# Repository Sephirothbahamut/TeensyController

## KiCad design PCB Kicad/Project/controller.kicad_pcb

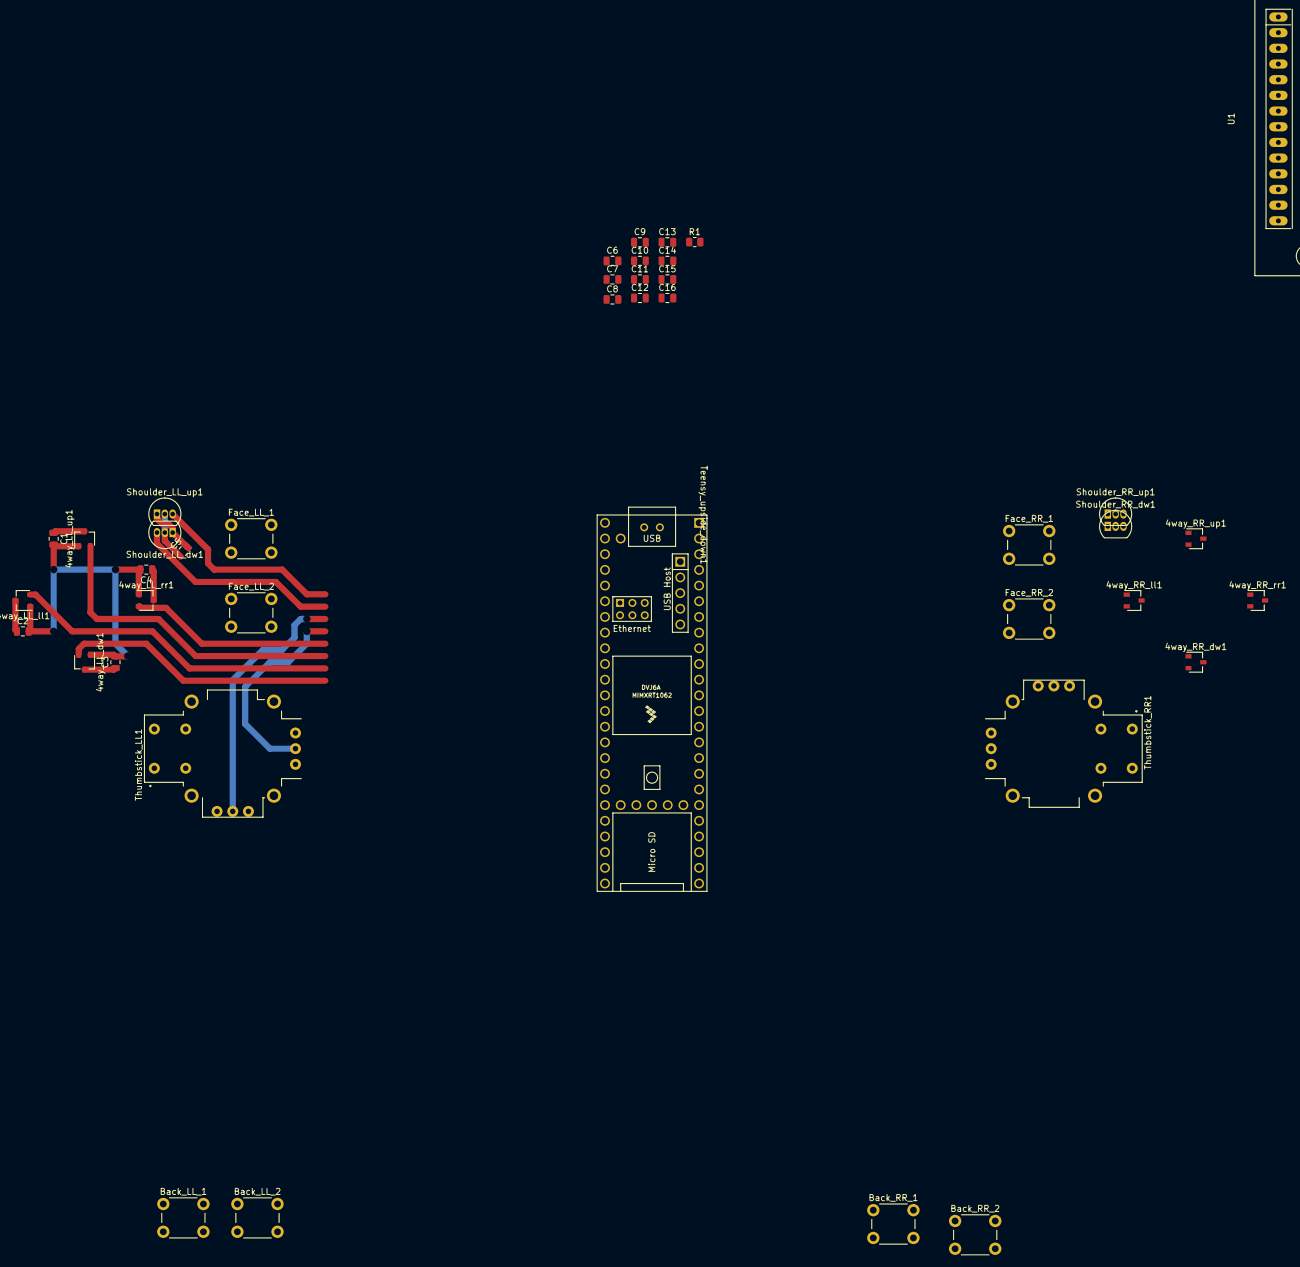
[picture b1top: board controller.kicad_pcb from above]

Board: 2 copper layers, 41 parts (0 on the bottom side), 32 nets.

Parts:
4way_LL_dw1, 4way_LL_ll1, 4way_LL_rr1, 4way_LL_up1, 4way_RR_dw1, 4way_RR_ll1, 4way_RR_rr1, 4way_RR_up1: A3214ELHLT-T; SOT-23W
Back_LL_1, Back_LL_2: SW_MEC_5E; SW_PUSH_6mm
Back_RR_1, Back_RR_2: SW_MEC_5E; SW_PUSH_6mm
C1, C2, C3, C4, C5, C6, C7, C8, C9, C10, C11, C12, C13, C14, C15, C16: Capacitor_SMD; C_0805_2012Metric
Face_LL_1, Face_LL_2: SW_MEC_5E; SW_PUSH_6mm
Face_RR_1, Face_RR_2: SW_MEC_5E; SW_PUSH_6mm
R1: Resistor 100ohm; R_0805_2012Metric
Shoulder_LL_dw1: DRV5055A3xLPGxQ1; TO-92_Inline
Shoulder_LL_up1: DRV5055A3xLPGxQ1; TO-92_Inline
Shoulder_RR_dw1: DRV5055A3xLPGxQ1; TO-92_Inline
Shoulder_RR_up1: DRV5055A3xLPGxQ1; TO-92_Inline
Teensy_upside_down1: Teensy4.1; Teensy41_upside_down
Thumbstick_LL1: Thumbstick; XDCR_COM-09032
Thumbstick_RR1: Thumbstick; XDCR_COM-09032
U1: TFT_320x240; TFT-320x240

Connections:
unnamed: 4way_LL_dw1.3 (GND), 4way_LL_ll1.3 (GND), 4way_LL_rr1.3 (GND), 4way_LL_up1.3 (GND), Back_LL_1.1, Back_LL_1.2, Back_LL_2.1, Back_LL_2.2, C1.1, C2.1, C3.1, C4.1, C5.1, C6.1, C7.1, C8.1, Face_LL_1.1, Face_LL_1.2, Face_LL_2.1, Face_LL_2.2, Shoulder_LL_dw1.2 (GND), Shoulder_LL_up1.2 (GND), Teensy_upside_down1.47 (GND), Thumbstick_LL1.B2A (SEL-), Thumbstick_LL1.H3 (H-), Thumbstick_LL1.S1 (SHIELD), Thumbstick_LL1.S2 (SHIELD), Thumbstick_LL1.S3 (SHIELD), Thumbstick_LL1.S4 (SHIELD), Thumbstick_LL1.V3 (V-)
unnamed: 4way_LL_dw1.1 (VCC), 4way_LL_ll1.1 (VCC), 4way_LL_rr1.1 (VCC), 4way_LL_up1.1 (VCC), C1.2, C2.2, C3.2, C4.2, C5.2, C6.2, C7.2, C8.2, Shoulder_LL_dw1.1 (VCC), Shoulder_LL_up1.1 (VCC), Teensy_upside_down1.46 (3V3), Thumbstick_LL1.H1 (H+), Thumbstick_LL1.V1 (V+), U1.4 (RST)
unnamed: 4way_LL_dw1.2 (VOUT), Teensy_upside_down1.30 (38_CS1_IN1)
unnamed: 4way_LL_ll1.2 (VOUT), Teensy_upside_down1.31 (39_MISO1_OUT1A)
unnamed: 4way_LL_rr1.2 (VOUT), Teensy_upside_down1.33 (41_A17)
unnamed: 4way_LL_up1.2 (VOUT), Teensy_upside_down1.32 (40_A16)
unnamed: 4way_RR_dw1.3 (GND), 4way_RR_ll1.3 (GND), 4way_RR_rr1.3 (GND), 4way_RR_up1.3 (GND), Back_RR_1.1, Back_RR_1.2, Back_RR_2.1, Back_RR_2.2, C9.1, C10.1, C11.1, C12.1, C13.1, C14.2, C15.1, C16.2, Face_RR_1.1, Face_RR_1.2, Face_RR_2.1, Face_RR_2.2, Shoulder_RR_dw1.2 (GND), Shoulder_RR_up1.2 (GND), Teensy_upside_down1.1 (GND), Thumbstick_RR1.B2A (SEL-), Thumbstick_RR1.H3 (H-), Thumbstick_RR1.S1 (SHIELD), Thumbstick_RR1.S2 (SHIELD), Thumbstick_RR1.S3 (SHIELD), Thumbstick_RR1.S4 (SHIELD), Thumbstick_RR1.V3 (V-)
unnamed: 4way_RR_dw1.1 (VCC), 4way_RR_ll1.1 (VCC), 4way_RR_rr1.1 (VCC), 4way_RR_up1.1 (VCC), C9.2, C10.2, C11.2, C12.2, C13.2, C14.1, C15.2, C16.1, Shoulder_RR_dw1.1 (VCC), Shoulder_RR_up1.1 (VCC), Teensy_upside_down1.15 (3V3), Thumbstick_RR1.H1 (H+), Thumbstick_RR1.V1 (V+)
unnamed: 4way_RR_dw1.2 (VOUT), Teensy_upside_down1.16 (24_A10_TX6_SCL2)
unnamed: 4way_RR_ll1.2 (VOUT), Teensy_upside_down1.17 (25_A11_RX6_SDA2)
unnamed: 4way_RR_rr1.2 (VOUT), Teensy_upside_down1.19 (27_A13_SCK1)
unnamed: 4way_RR_up1.2 (VOUT), Teensy_upside_down1.18 (26_A12_MOSI1)
unnamed: Shoulder_LL_dw1.3 (OUT), Teensy_upside_down1.40 (18_A4_SDA)
unnamed: Shoulder_LL_up1.3 (OUT), Teensy_upside_down1.41 (19_A5_SCL)
unnamed: Shoulder_RR_dw1.3 (OUT), Teensy_upside_down1.45 (23_A9_CRX1_MCLK1)
unnamed: Shoulder_RR_up1.3 (OUT), Teensy_upside_down1.44 (22_A8_CTX1)
unnamed: Teensy_upside_down1.4 (2_OUT2), U1.14
unnamed: Teensy_upside_down1.10 (8_TX2_IN1), U1.11
unnamed: Teensy_upside_down1.11 (9_OUT1C), U1.5 (DC), U1.12
unnamed: Teensy_upside_down1.12 (10_CS_MQSR), U1.3 (CS)
unnamed: Teensy_upside_down1.13 (11_MOSI_CTX1), U1.6 (MOSI)
unnamed: Teensy_upside_down1.14 (12_MISO_MQSL), U1.9 (MISO), U1.13
unnamed: Teensy_upside_down1.35 (13_SCK_LED), U1.7 (SCK), U1.10
unnamed: Teensy_upside_down1.38 (16_A2_RX4_SCL1), Thumbstick_LL1.H2 (H)
unnamed: Teensy_upside_down1.39 (17_A3_TX4_SDA1), Thumbstick_LL1.V2 (V)
unnamed: Teensy_upside_down1.42 (20_A6_TX5_LRCLK1), Thumbstick_RR1.H2 (H)
unnamed: Teensy_upside_down1.43 (21_A7_RX5_BCLK1), Thumbstick_RR1.V2 (V)
unnamed: Teensy_upside_down1.20 (28_RX7), Thumbstick_RR1.B1A (SEL+)
unnamed: Teensy_upside_down1.29 (37_CS), Thumbstick_LL1.B1A (SEL+)
unnamed: R1.1, Teensy_upside_down1.48 (VIN), U1.1 (VCC)
unnamed: Teensy_upside_down1.34 (GND), U1.2 (GND)
unnamed: R1.2, U1.8 (LED)

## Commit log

2022-07-26 started ui
2023-07-01 added hardware side stuff
2023-07-02 reworked button cluster 3d model
2023-07-02 added thumbstick reference
2023-07-02 added more references, centered TFT display
2023-07-12 added shoulder buttons support
2023-07-13 I renounced trying to make a curved shell in freecad, welcome to the party blender XD
2023-07-17 added SMD hall sensor model
2023-07-20 first attempt at custom mesh, added xbox controller reference
2023-08-30 changed shoulders positions
